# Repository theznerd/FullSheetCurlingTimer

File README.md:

# 🥌🥌🥌 Full Sheet Curling Timer 🥌🥌🥌

The purpose of this repository is to explore an inexpensive, ESP32-based, laser
trip timer for full sheet timing (4 lasers, 2 at each back line and 2 at each
hog line). Access to the times recorded by the timer is provided via a simple
web interface that connects to an ESP32 using the Web Bluetooth API. One ESP32
acts as a BLE Peripheral that hosts a custom GATT service for the timer, and all
four ESP32 devices will act as event detectors (laser trip detection) which
communicate the event data via ESP-NOW protocol to be picked up by the BLE
peripheral.

## License

This project is licensed under the Business Source License 1.1 (BUSL).
You may use it freely for noncommercial purposes.
For commercial use, please contact [nathan@z-nerd.com](mailto:nathan@z-nerd.com)
to obtain a commercial license.

## Goals

- **💸 Low-cost hardware**: inexpensive components (e.g., ESP32, laser modules)
  to keep single sheet cost under $150 (less when building for multiple sheets).
- **✅ Easy fabrication**: 3D-printable enclosure and PCBs for hobbyist skill
  level assembly (or schematics for breadboard assembly).
- **⏱️ Accurate timing**: millisecond-level accuracy for splits.
- **⚙️ Easy Setup and Use**: non-technical friendly setup and operation with
  guidance for setup and calibration provided in the web UI.
- **👀 Full sheet support**: support dual split timing (back line to hog line,
  and hog line to hog line) and bi-directional throws without moving hardware.
- **👨‍👩‍👧‍👦 Multi-viewer support**: allow multiple phones/tablets to connect and view
  timing data simultaneously.
- **🌐 Native App**: simple native app accessible from any modern platform
  with Bluetooth support - no cloud services, no complicated Wi-Fi setup for
  devices.

## Architecture (Multi-viewer)

### Roles and data flow

- **Main Timer and Laser Sensor - ESP32 = BLE Peripheral (GATT Server)**
  - Advertises a custom "Timer Service" so clients can discover it.
  - Has an assigned sheet ID (via dip switches) for identification.
  - Has an assigned placement ID (via dip switches) for sheet position.
  - Receives laser trip events from self and secondary timer devices (ESP-NOW).
  - Hosts characteristics for state + events.
  - Pushes timing updates using **notifications**.

- **Secondary Timer Devices - ESP32s = ESP-NOW Sender**
  - Has an assigned sheet ID (via dip switches) for identification.
  - Has an assigned placement ID (via dip switches) for sheet position.
  - Communicates laser trip events via ESP-NOW protocol.

- **Viewer (browser/web UI) = BLE Central (GATT Client)**
  - Scans for timer devices (filtered by name/service UUID).
  - Connects to **one** timer device at a time.
  - Provides diagnostics and setup UI.
  - Reads current timer state upon connection.
  - Subscribes to notifications to receive live updates.

This pattern supports multiple viewers concurrently: each viewer connects and
enables notifications independently.

### BLE Advertising For Viewer Discovery

To make it easy to pick the right timer when multiple devices are nearby, each
device should include clear identity in advertising:

- **Device name**: e.g., `CurlTimer Sheet 3`
- **Advertised Service UUID**: `Timer Service` (custom UUID)
- **Optional service/manufacturer data**: e.g., `sheetId`, `deviceId`,
  `firmwareVersion`

### GATT Service Model (proposed)

GATT is used for structured data exchange between the timer device and viewer.
GATT is well-suited for this use case due to its efficient notification
mechanism for real-time updates. Implementation details are discussed in the
[firmware design decisions](Firmware/design_decisions.md) document.

### Device-to-Device ESP-NOW Communication Model

ESP-NOW is the proposed protocol for communication between the laser sensors
and the main timer device. ESP-NOW was considered over BLE Advertising due to
better reliability and lower latency. Implementation details are discussed in
the [firmware design decisions](Firmware/design_decisions.md) document.

### Notes for future consideration

- WebKit has no support (actively opposes) for the Web Bluetooth API, and all
  iOS browsers are forced to use WebKit (with the exception of EU member
  states). Therefore, iOS support is not feasible with the current Web Bluetooth
  API limitations. Need to switch to a native app, which will bring added
  complexity. Looking at Avalonia for cross-platform native app development.
- It is possible to infer the direction of travel from the sequence of laser
  trip events, so that a stone passing the opposing back line does not cause a
  new timing event. However, this may be error-prone if stones are being thrown
  closely together in timing in opposite directions. Explicit direction setting
  from the viewer may be more reliable but requires user interaction which may
  be inconvenient or undesirable during practice.
- It may be useful to calculate the rock speed at each trip point and include
  that in the event data sent to viewers.
- **Timing accuracy note**: ESP-NOW retries/bursts improve delivery reliability
  but can add variable *arrival latency*. To keep recorded split times accurate,
  trip events should include a **sender-side capture timestamp** (taken at the
  instant the beam transition is detected), and the main timer should map that
  to its own clock using a lightweight beacon-based offset estimate.

## Wish List

- [ ] Apple WatchOS App for on-ice timing
- [ ] Garmin Connect IQ App for on-ice timing

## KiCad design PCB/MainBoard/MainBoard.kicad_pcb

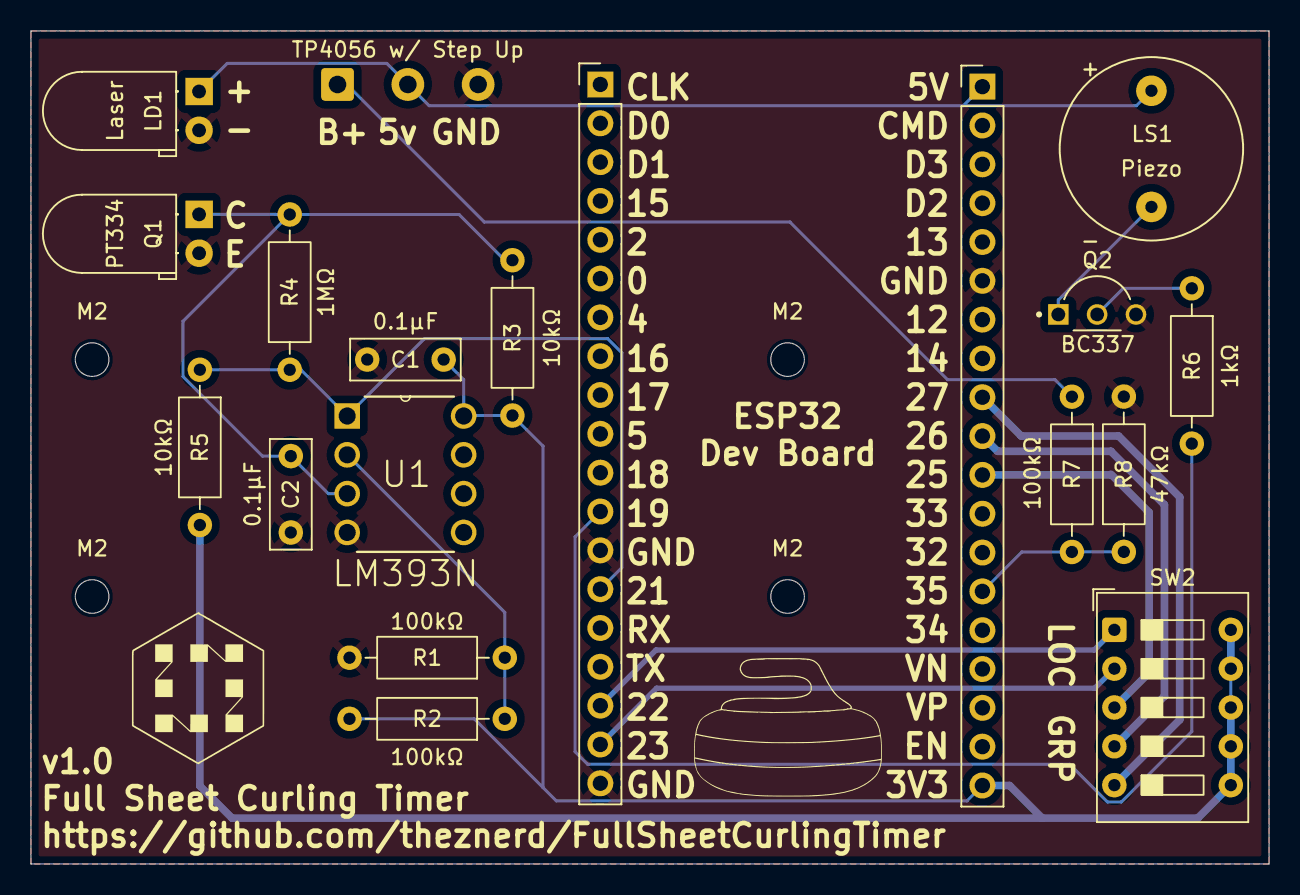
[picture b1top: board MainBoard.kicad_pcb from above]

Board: 2 copper layers, 81.0 x 54.5 mm, 23 parts (0 on the bottom side), 16 nets.

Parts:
 : PinHeader_1x19_P2.54mm_Vertical
 #2: PinHeader_1x19_P2.54mm_Vertical
C1, C2: 0.1µF; C_Disc_D7.0mm_W2.5mm_P5.00mm
LD1: Laser; LED_D5.0mm_Horizontal_O1.27mm_Z3.0mm_Clear
LS1: Piezo; CUI_CMI-1295IC-0585T
M2, M2#2, M2#3, M2#4: MountingHole_2.2mm_M2
Q1: PT334; LED_D5.0mm_Horizontal_O1.27mm_Z3.0mm_Clear
Q2: BC337; TO92254P480H870-3
R1, R2, R7: 100kΩ; R_Axial_DIN0207_L6.3mm_D2.5mm_P10.16mm_Horizontal
R3, R5: 10kΩ; R_Axial_DIN0207_L6.3mm_D2.5mm_P10.16mm_Horizontal
R4: 1MΩ; R_Axial_DIN0207_L6.3mm_D2.5mm_P10.16mm_Horizontal
R6: 1kΩ; R_Axial_DIN0207_L6.3mm_D2.5mm_P10.16mm_Horizontal
R8: 47kΩ; R_Axial_DIN0207_L6.3mm_D2.5mm_P10.16mm_Horizontal
SW2: SW_DIP_x05; SW_DIP_SPSTx05_Slide_9.78x14.88mm_W7.62mm_P2.54mm
TP4056 w/ Step Up: SolderWire-0.5sqmm_1x03_P4.6mm_D0.9mm_OD2.1mm
U1: LM393N; DIP254P762X508-8

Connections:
+3V3: .19, C1.1, R2.2, R3.2, R5.2, SW2.6, SW2.7, SW2.8, SW2.9, SW2.10, U1.8
+5V In PCB: .1, LD1.1 (K), LS1.P, TP4056 w/ Step Up.2
GND: .6, #2.13, #2.19, C1.2, C2.2, LD1.2 (A), Q1.2 (E), Q2.3 (E), R1.2, R8.2, TP4056 w/ Step Up.3, U1.4
unnamed: C2.1, Q1.1 (C), R3.1, R4.2, U1.3
unnamed: Q2.2 (B), R6.1
unnamed: LS1.N, Q2.1 (C)
unnamed: #2.14, R4.1, R5.1, U1.1
unnamed: #2.12, R6.2
unnamed: R7.1, TP4056 w/ Step Up.1
unnamed: .14, R7.2, R8.1
unnamed: #2.17, SW2.1
unnamed: #2.18, SW2.2
unnamed: .11, SW2.3
unnamed: .10, SW2.4
unnamed: .9, SW2.5
unnamed: R1.1, R2.1, U1.2

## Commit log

2025-12-16 concept documentation
2025-12-16 cleanup of leftovers from change from BLE adverts to ESP-NOW
2025-12-16 some initial design consideration documentation
2025-12-17 more design considerations and an initial pass at stone sequence... testing out KiCad as PCB and schematic design solution
2025-12-17 changes to readme
2025-12-21 Refactor README and add user journey documentation for curling timer system
    - Updated GATT service model section in README to emphasize structured data exchange and real-time updates.
    - Created a semi-comprehensive user journey document detailing preconfiguration, setup, operation, and maintenance processes for the curling timer system.
2025-12-21 Update BOM.md with corrected links for LM393 Comparator and other components
2025-12-21 Update LAST UPDATED date in BOM.md to reflect the latest revision
2025-12-21 (CO-PILOT) Initialize web application with Bluetooth functionality.
    - Added package.json for project configuration and dependencies.
    - Implemented main.ts for handling Bluetooth device connections and UI interactions.
    - Created style.css for basic styling of the application.
    - Configured TypeScript with tsconfig.json for strict type checking and module resolution.
    - Set up Vite configuration in vite.config.ts for building and serving the application.
2025-12-21 Removing vite web app. WebKit is actively hostile toward Web Bluetooth API. Moving to cross platform native app.
2025-12-21 I'm more comfortable with C#
2025-12-23 - Implemented Framework for Mobile App - Created Wishlist (Added Apple WatchOS and Garmin Connect IQ App)
2025-12-23 Fix link reference
2025-12-23 Add firmware boilerplate
2025-12-28 Some initial bootstrapping of the firmware
2025-12-29 Iniital schematic (poor layout), and added additional functionality to the firmware
2025-12-29 rename project and add version.txt for better tracking
2025-12-29 Add readme to firmware, and update diagnostics readme
2025-12-30 Lots of changes - initial pcb layout without wires
2025-12-30 PCB v1.0 - schematic needs review still in comparison to PCB - initial order of PCBs with JLCPCB. Updated BOM to reflect actual resistor/capacitor count.
2025-12-31 Ran into issues in breadboarding - hoping r2 of PCB fixes. Luckily caught the order in time to get new files uploaded so order was not wasted.
2025-12-31 Gerber files probably need to be updated again (apparently dimensions were on the copper layer - did not cause grief with JLCPCB). BOM updated with OSHPark quote.
2026-01-06 First PCBs are in - and they test well... putting test enclosure together now test fit and function.
2026-01-08 Add some test iterations of the enclosure, and add a basic test to the firmware (beep on change of beam state)
2026-01-08 Basic GATT test for field test of unit on Saturday
2026-01-10 Revise design decisions and add field test notes
    Updated the design decisions document with notes from field tests and marked component dimensions as verified.
2026-01-10 Update design decisions for laser alignment
    Added recommendation to improve laser alignment stability.
2026-01-24 A lot more tests - but believe I've landed on a prototype. Will test more at the club
2026-01-27 Well, developing for Garmin is easier than imagined... going to start with it since I've got myself a Garmin watch...
2026-01-28 Before I let the agent get to work...
